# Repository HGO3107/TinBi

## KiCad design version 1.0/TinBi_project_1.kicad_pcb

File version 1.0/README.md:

# TinBi
This repo contains the files that are related to hardware classes

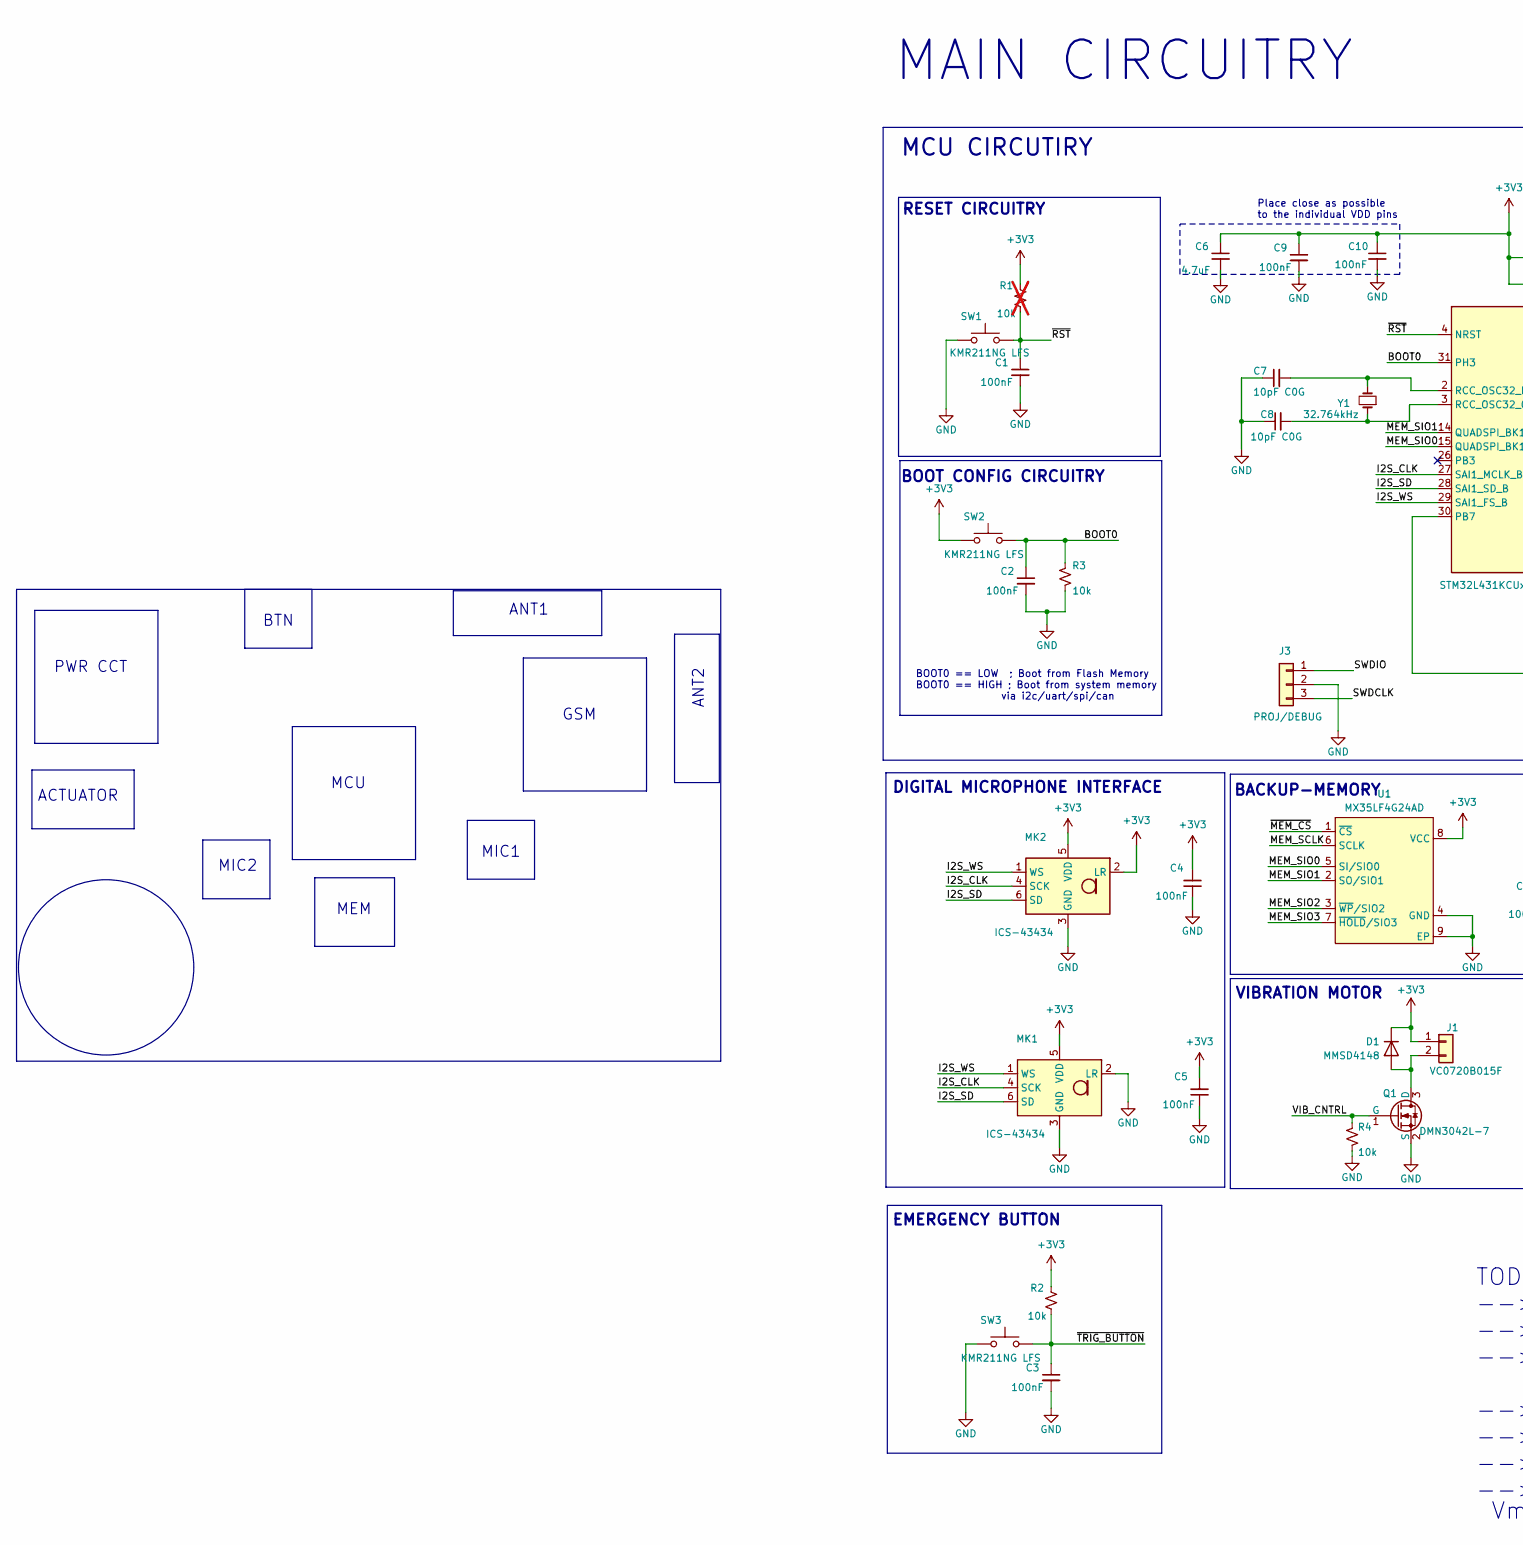
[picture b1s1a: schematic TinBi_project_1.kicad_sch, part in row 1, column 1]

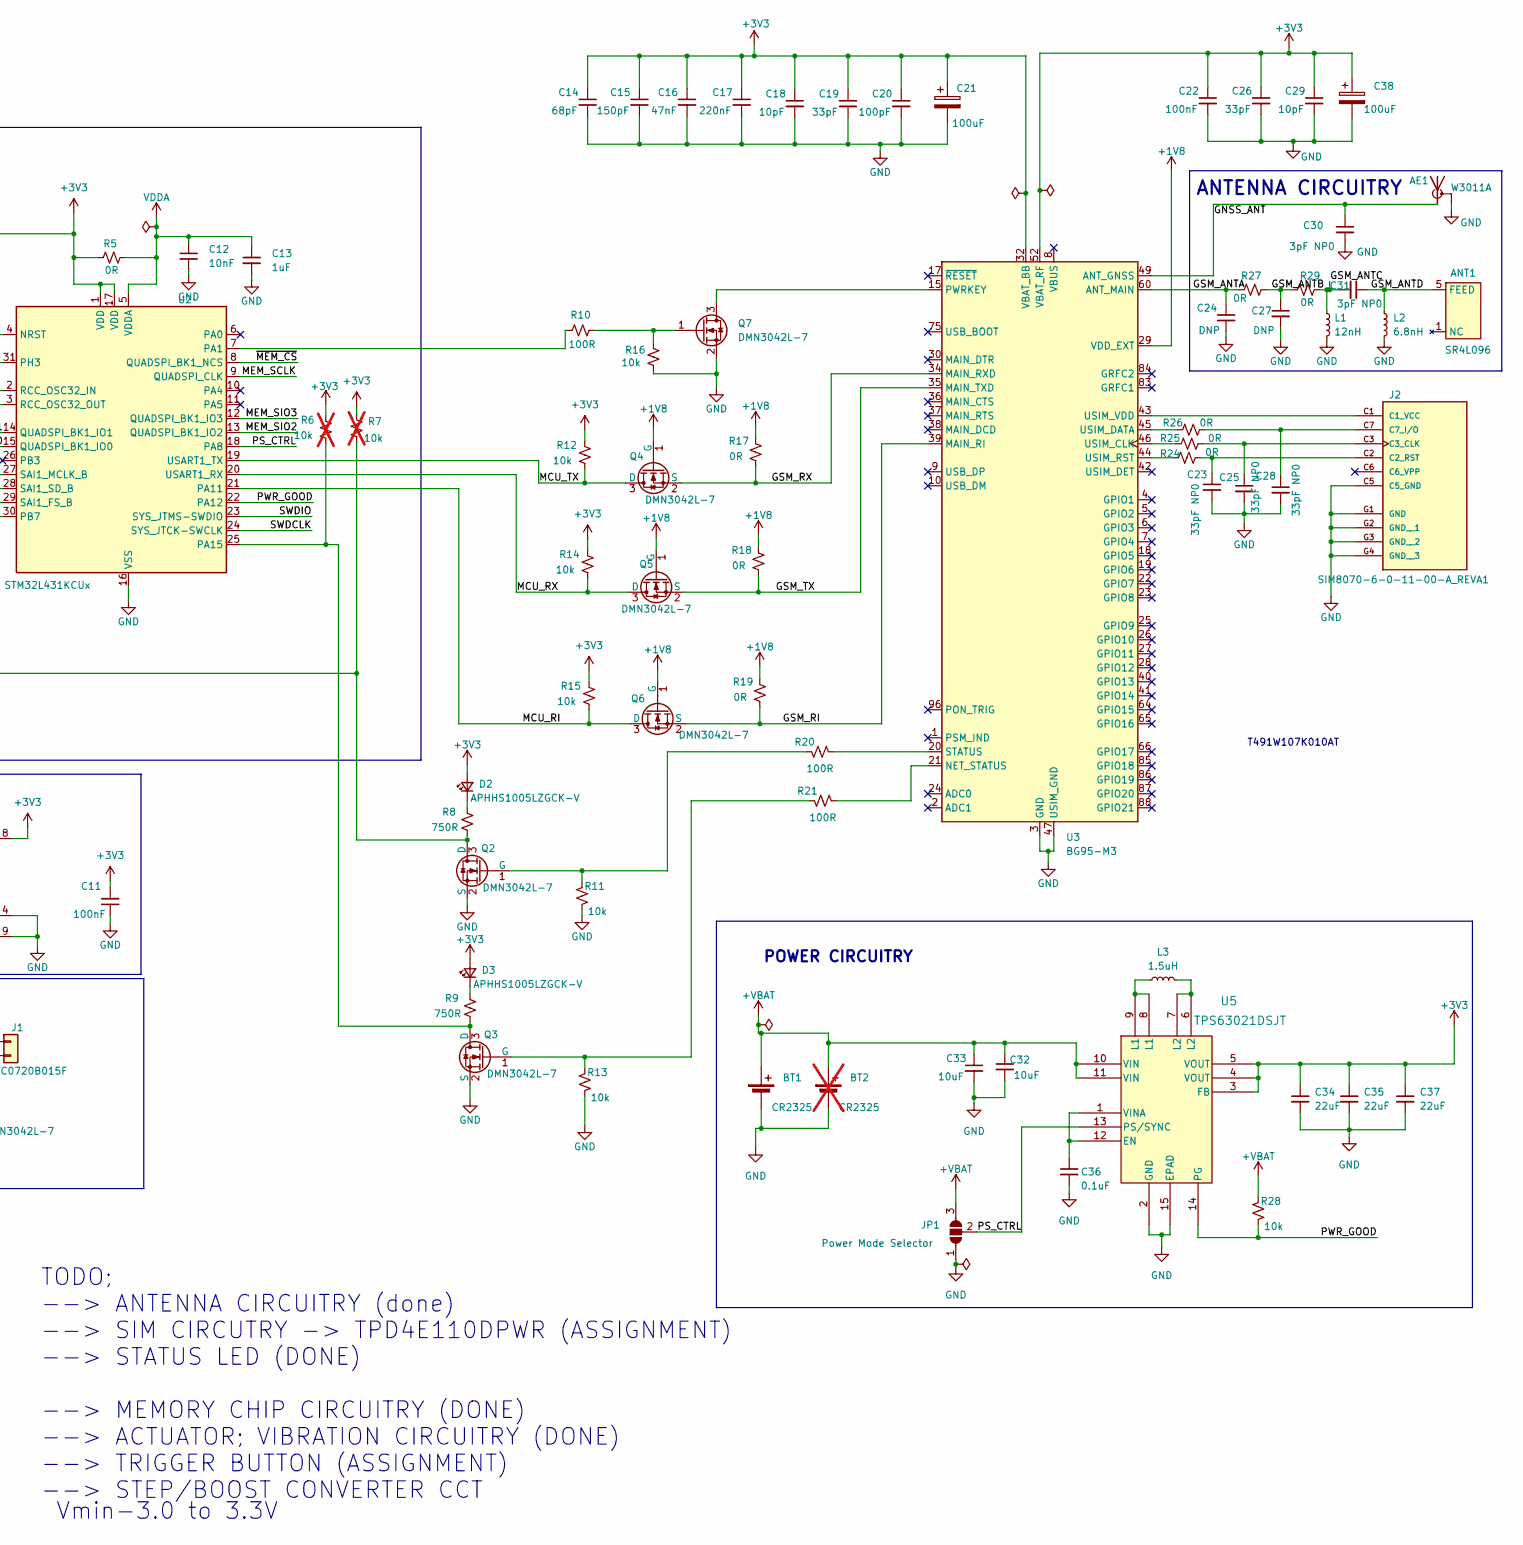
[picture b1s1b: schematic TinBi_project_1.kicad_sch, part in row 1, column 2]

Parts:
AE1: W3011A; Pulse_W3011
ANT1: SR4L096; SR4L09
BT1: CR2325; BatteryHolder_ComfortableElectronic_CH273-2450_1x2450
BT2: CR2325; BatteryHolder_ComfortableElectronic_CH273-2450_1x2450; not fitted
C1, C2, C3, C4, C5, C9, C10, C11, C22: 100nF; C_0402_1005Metric
C6: 4.7uF; C_0805_2012Metric
C7, C8: 10pF C0G; C_0402_1005Metric
C12: 10nF; C_0402_1005Metric
C13: 1uF; C_0402_1005Metric
C14: 68pF; C_0402_1005Metric
C15: 150pF; C_0402_1005Metric
C16: 47nF; C_0402_1005Metric
C17: 220nF; C_0402_1005Metric
C18, C29: 10pF; C_0402_1005Metric
C19, C26: 33pF; C_0402_1005Metric
C20: 100pF; C_0402_1005Metric
C21: 100uF; CP_EIA-7343-15_Kemet-W; MPN T491W107K010AT
C23, C25, C28: 33pF NP0; C_0402_1005Metric
C24, C27: DNP; C_0402_1005Metric
C30: 3pF NP0; C_0402_1005Metric
C31: 3pF NP0; C_0603_1608Metric
C32, C33: 10uF; C_0805_2012Metric; MPN CL21B106KAYQNNE
C34, C35, C37: 22uF; C_0805_2012Metric; MPN GRM21BZ71A226ME15L
C36: 0.1uF; C_0402_1005Metric
C38: 100uF; CP_EIA-7343-15_Kemet-W
D1: MMSD4148; D_SOD-123
D2, D3: APHHS1005LZGCK-V; LED_0603_1608Metric
J1: VC0720B015F; 3mm by 3mm pad
J2: SIM8070-6-0-11-00-A_REVA1; GCT_SIM8070-6-0-11-00-A_REVA1; PARTREV A1
J3: PROJ/DEBUG; PinHeader_1x03_P2.54mm_Vertical
JP1: Power Mode Selector; SolderJumper-3_P1.3mm_Open_RoundedPad1.0x1.5mm
L1: 12nH; L_0402_1005Metric; MPN AIMC-0402HQ-12NG-T
L2: 6.8nH; L_0402_1005Metric; MPN ASCH001005056N8JCP
L3: 1.5uH; L_Coilcraft_XAL4020-XXX; MPN XFL4020-152MEC
MK1, MK2: ICS-43434; InvenSense_ICS-43434-6_3.5x2.65mm
Q1, Q2, Q3, Q4, Q5, Q6, Q7: DMN3042L-7; SOT-23
R1, R6, R7: 10k; R_0603_1608Metric; not fitted
R2, R3, R4, R11, R12, R13, R14, R15, R16, R28: 10k; R_0603_1608Metric
R5, R17, R18, R19, R24, R25, R26, R27, R29: 0R; R_0603_1608Metric
R8, R9: 750R; R_0603_1608Metric
R10, R20, R21: 100R; R_0603_1608Metric
SW1, SW2, SW3: KMR211NG LFS; SW_Push_1P1T_NO_CK_KMR2
U1: MX35LF4G24AD; WSON-8-1EP_8x6mm_P1.27mm_EP3.4x4.3mm
U2: STM32L431KCUx; QFN-32-1EP_5x5mm_P0.5mm_EP3.45x3.45mm
U3: BG95-M3; Quectel_BG95
U5: TPS63021DSJT; IC_TPS63020DSJT
Y1: 32.764kHz; XTAL_ABM2-25.000MHZ-D4Y-T

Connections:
+1V8: Q4.1 (G), Q5.1 (G), Q6.1 (G), R17.2, R18.2, R19.2, U3.29 (VDD_EXT)
+3V3: C4.2, C5.2, C6.1, C9.1, C10.1, C11.2, C14.1, C15.1, C16.1, C17.1, C18.1, C19.1, C20.1, C21.1, C22.1, C26.1, C29.1, C34.1, C35.1, C37.1, C38.1, D1.1 (K), D2.2 (A), D3.2 (A), J1.1, MK1.5 (VDD), MK2.2 (LR), MK2.5 (VDD), R1.2, R2.2, R5.1, R6.2, R7.2, R12.2, R14.2, R15.2, SW2.1, U1.8 (VCC), U2.1 (VDD), U2.17 (VDD), U3.32 (VBAT_BB), U3.33 (VBAT_BB), U3.52 (VBAT_RF), U3.53 (VBAT_RF), U5.3 (FB), U5.4 (VOUT), U5.5 (VOUT)
+VBAT: BT1.1 (+), BT2.1 (+), C32.1, C33.1, JP1.3 (B), R28.2, U5.10 (VIN), U5.11 (VIN)
/BOOT0: C2.1, R3.2, SW2.2, U2.31 (PH3)
/GNSS_ANT: AE1.1 (A), C30.1, U3.49 (ANT_GNSS)
/GSM_ANTA: C24.1, R27.2, U3.60 (ANT_MAIN)
/GSM_ANTB: C27.1, R27.1, R29.2
/GSM_ANTC: C31.2, L1.1, R29.1
/GSM_ANTD: ANT1.5 (FEED), C31.1, L2.1
/GSM_RI: Q6.2 (S), R19.1, U3.39 (MAIN_RI)
/GSM_RX: Q4.2 (S), R17.1, U3.34 (MAIN_RXD)
/GSM_TX: Q5.2 (S), R18.1, U3.35 (MAIN_TXD)
/I2S_CLK: MK1.4 (SCK), MK2.4 (SCK), U2.27 (SAI1_MCLK_B)
/I2S_SD: MK1.6 (SD), MK2.6 (SD), U2.28 (SAI1_SD_B)
/I2S_WS: MK1.1 (WS), MK2.1 (WS), U2.29 (SAI1_FS_B)
/MCU_RI: Q6.3 (D), R15.1, U2.21 (PA11)
/MCU_RX: Q5.3 (D), R14.1, U2.20 (USART1_RX)
/MCU_TX: Q4.3 (D), R12.1, U2.19 (USART1_TX)
/MEM_SCLK: U1.6 (SCLK), U2.9 (QUADSPI_CLK)
/MEM_SIO0: U1.5 (SI/SIO0), U2.15 (QUADSPI_BK1_IO0)
/MEM_SIO1: U1.2 (SO/SIO1), U2.14 (QUADSPI_BK1_IO1)
/MEM_SIO2: U1.3 (~WP/SIO2), U2.13 (QUADSPI_BK1_IO2)
/MEM_SIO3: U1.7 (~HOLD/SIO3), U2.12 (QUADSPI_BK1_IO3)
/PS_CTRL: JP1.2 (C), U2.18 (PA8), U5.13 (PS/SYNC)
/PWR_GOOD: R28.1, U2.22 (PA12), U5.14 (PG)
/SWDCLK: J3.3, U2.24 (SYS_JTCK-SWCLK)
/SWDIO: J3.1, U2.23 (SYS_JTMS-SWDIO)
/VIB_CNTRL: Q1.1 (G), R4.2
/~MEM_CS: U1.1 (~CS), U2.8 (QUADSPI_BK1_NCS)
/~RST: C1.1, R1.1, SW1.2, U2.4 (NRST)
/~TRIG_BUTTON: C3.1, R2.1, SW3.2
GND: AE1.2 (GND), BT1.2 (-), BT2.2 (-), C1.2, C2.2, C3.2, C4.1, C5.1, C6.2, C7.1, C8.1, C9.2, C10.2, C11.1, C12.2, C13.2, C14.2, C15.2, C16.2, C17.2, C18.2, C19.2, C20.2, C21.2, C22.2, C23.2, C24.2, C25.2, C26.2, C27.2, C28.2, C29.2, C30.2, C32.2, C33.2, C34.2, C35.2, C36.2, C37.2, C38.2, J2.C5 (C5_GND), J2.G1 (GND), J2.G2 (GND__1), J2.G3 (GND__2), J2.G4 (GND__3), J3.2, JP1.1 (A), L1.2, L2.2, MK1.2 (LR), MK1.3 (GND), MK2.3 (GND), Q1.2 (S), Q2.2 (S), Q3.2 (S), Q7.2 (S), R3.1, R4.1, R11.1, R13.1, R16.1, SW1.1, SW3.1, U1.4 (GND), U1.9 (EP), U2.16 (VSS), U2.32 (VSS), U2.33 (VSS), U3.3 (GND), U3.31 (GND), U3.47 (USIM_GND), U3.48 (GND), U3.50 (GND), U3.54 (GND), U3.55 (GND), U3.58 (GND), U3.59 (GND), U3.61 (GND), U3.62 (GND), U3.67 (GND), U3.68 (GND), U3.69 (GND), U3.70 (GND), U3.71 (GND), U3.72 (GND), U3.73 (GND), U3.74 (GND), U3.79 (GND), U3.80 (GND), U3.81 (GND), U3.82 (GND), U3.89 (GND), U3.90 (GND), U3.91 (GND), U3.100 (GND), U3.101 (GND), U3.102 (GND), U5.2 (GND), U5.15 (EPAD)
unnamed: D1.2 (A), J1.2, Q1.3 (D)
unnamed: D2.1 (K), R8.2
unnamed: D3.1 (K), R9.2
unnamed: J2.C1 (C1_VCC), U3.43 (USIM_VDD)
unnamed: C23.1, J2.C2 (C2_RST), R24.2
unnamed: C25.1, J2.C3 (C3_CLK), R25.2
unnamed: C28.1, J2.C7 (C7_I/O), R26.2
unnamed: L3.1, U5.8 (L1), U5.9 (L1)
unnamed: L3.2, U5.6 (L2), U5.7 (L2)
unnamed: Q2.3 (D), R7.1, R8.1, U2.30 (PB7)
unnamed: Q2.1 (G), R11.2, R20.2
unnamed: Q3.3 (D), R6.1, R9.1, U2.25 (PA15)
unnamed: Q3.1 (G), R13.2, R21.2
unnamed: Q7.3 (D), U3.15 (PWRKEY)
unnamed: Q7.1 (G), R10.1, R16.2
unnamed: R10.2, U2.7 (PA1)
unnamed: C7.2, U2.2 (RCC_OSC32_IN), Y1.2
unnamed: C8.2, U2.3 (RCC_OSC32_OUT), Y1.1
unnamed: R21.1, U3.21 (NET_STATUS)
unnamed: R20.1, U3.20 (STATUS)
unnamed: R25.1, U3.46 (USIM_CLK)
unnamed: R26.1, U3.45 (USIM_DATA)
unnamed: R24.1, U3.44 (USIM_RST)
unnamed: C36.1, U5.1 (VINA), U5.12 (EN)
VDDA: C12.1, C13.1, R5.2, U2.5 (VDDA)

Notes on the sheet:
BACKUP-MEMORY
EMERGENCY BUTTON
Vmin-3.0 to 3.3V
PWR CCT
VIBRATION MOTOR
TODO; --> ANTENNA CIRCUITRY (done) --> SIM CIRCUTRY -> TPD4E110DPWR (ASSIGNMENT) --> STATUS LED (DONE) --> MEMORY CHIP CIRCUITRY (DONE) --> ACTUATOR; VIBRATION CIRCUITRY (DONE) --> TRIGGER BUTTON (ASSIGNMENT) --> STEP/BOOST CONVERTER CCT
ANTENNA CIRCUITRY
MIC2
MEM
BOOT CONFIG CIRCUITRY
BTN
MCU
MCU CIRCUTIRY
DIGITAL MICROPHONE INTERFACE
ACTUATOR
ANT1
GSM
BOOT0 == LOW ; Boot from Flash Memory BOOT0 == HIGH ; Boot from system memory via i2c/uart/spi/can
MAIN CIRCUITRY
RESET CIRCUITRY
MIC1
POWER CIRCUITRY
Place close as possible to the individual VDD pins
T491W107K010AT
ANT2

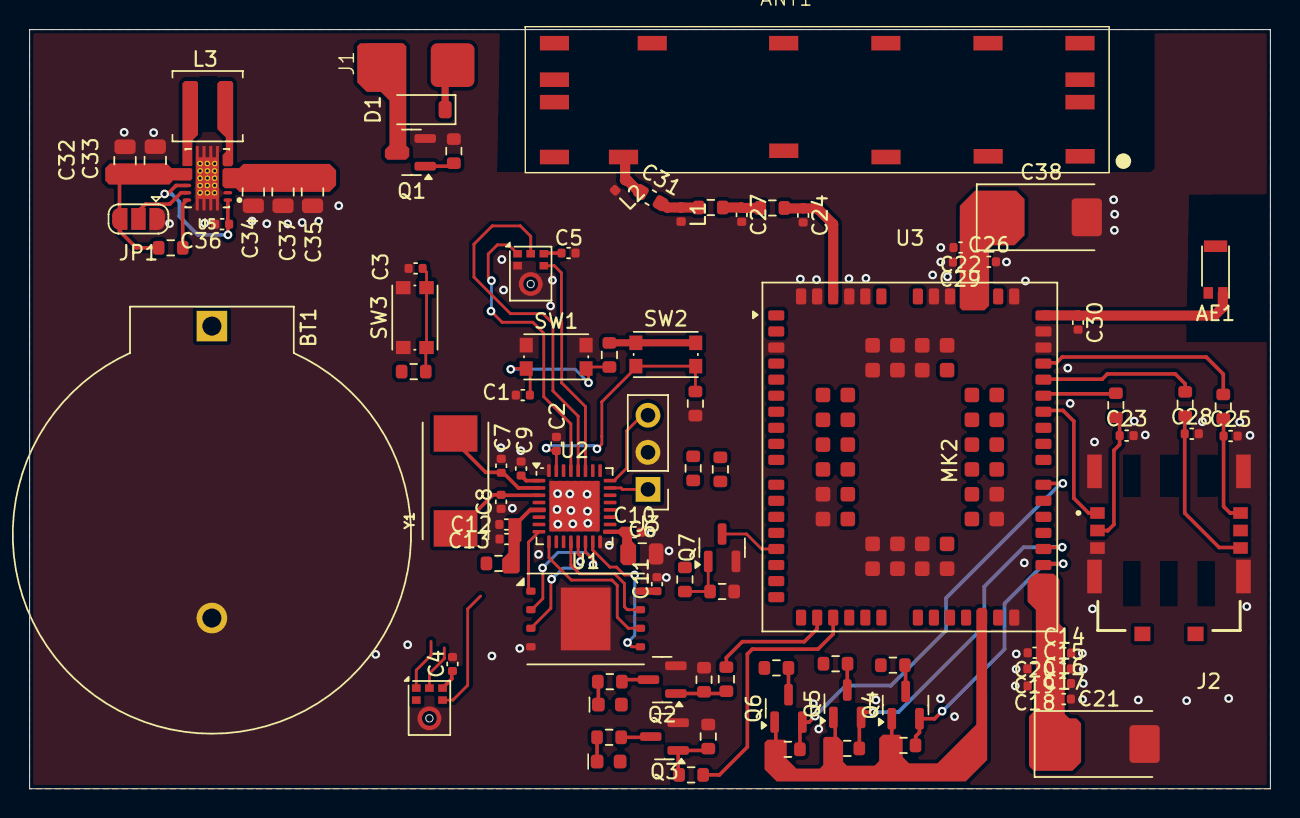
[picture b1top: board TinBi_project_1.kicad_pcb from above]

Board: 2 copper layers, 85.0 x 52.0 mm, 95 parts (0 on the bottom side), 57 nets.

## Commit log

2026-02-14 Updated with the antenna symbols and library
2026-02-22 Todo; TVS SIM circuitry, trigger button, and boost circuitry
2026-03-04 Updated designs
2026-03-30 Layout progress
